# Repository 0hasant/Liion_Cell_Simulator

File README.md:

# Cell Test Bench

Single-cell characterization bench for 18650 and 21700 Li-ion cells (DMEGC INR45E, generic 3.5 Ah 18650). The goal is a fitted **2RC equivalent-circuit model** (OCV, R0, R1/C1, R2/C2 versus SOC and temperature). Part of the Solaris final-year project.

- 0–10 A linear electronic load (constant current), down to 2.0 V
- Charging up to 5 A from a 30 V bench PSU through an XL4016 module, with voltage **and** current limit set by the MCU
- Bidirectional current on one 10 mΩ shunt with Kelvin taps; Kelvin cell voltage on a 16-bit ADS1115
- Cell held at about 10–45 °C in an insulated pocket, cooled or heated by two TEC1-12706 Peltiers
- STM32F103 Blue Pill, USB CDC to a Python UI
- Hardware protection (OV, UV, OC, OT) that latches and cuts relay and Peltier power without the firmware

## Status (v0.4, 2026-11-11)

| Item | State |
|---|---|
| Schematic | v0.4, 8 sheets, generated by `hardware/tools/design.py`. Netlist checked against KiCad's export (0 problems). All review items closed: `docs/CHANGES_v0.4.md` |
| Parts | Every part has a Turkish source with price and stock on 2026-11-10: `hardware/bom.csv` (board) and `hardware/bom_offboard.csv` (modules, mechanics). Total about 5,500 TL |
| PCB | 180 × 130 mm, **single-sided** for in-house CNC milling, through-hole parts plus two SMD parts on the copper side, wire jumpers where one layer is not enough |
| CNC files | `hardware/fab/`: Gerber + Excellon, mirrored SVGs for Luban, 1:1 print, jumper list, DRC report. How to mill: `docs/CNC_MILLING.md` |
| 3D | Electronics box and thermal unit in `mechanical/` (STL, STEP, renders). All printed parts fit a 220 × 220 mm bed, collision check clean |
| Built / tested | **No.** Bring-up plan: `docs/BRINGUP.md` |
| Firmware, UI | Not started |

## Repository layout

| Path | Contents |
|---|---|
| `hardware/kicad/` | KiCad project: open `cell_test_bench.kicad_pro` (KiCad 7 format, opens in KiCad 10) |
| `hardware/kicad/lib/` | Project footprint library and 3D models |
| `hardware/fab/` | Milling and drilling files |
| `hardware/bom.csv`, `bom_offboard.csv` | Priced BOM with Turkish shops and links |
| `hardware/tools/` | Scripts that generate the schematic, placement, routing, BOM and fab files |
| `mechanical/` | CadQuery enclosure: `enclosure.py`, `check.py`, STL, STEP, renders |
| `docs/` | Schematic guide, v0.4 changes, bring-up, milling, layout review, project sync |
| `firmware/`, `ui/` | Not started |

## Board overview

- **Left edge:** PSU input (J101), 12 V buck module (J102), charger module (J401), FB tap (J402).
- **Top edge:** thermostat (J104), fans (J704–J706), Peltier output (J702), Blue Pill with USB at the edge.
- **Right edge:** four NTC terminals (J501–J504).
- **Bottom edge:** cell power (J205), 0.1 Ω load resistor (J301), IRFP260N (Q301, tab facing out onto the load cooler), Kelvin sense (J206).
- `PGND` (power return) and `GND` (signal) are separate nets, joined at one wire link (JP201) next to the shunt.

## Blue Pill pin map

| Pin | Signal | Function |
|---|---|---|
| PA0 / PA1 | I_MON / V_FAST | ADC: fast current (1.71 V + 0.12 V/A), fast cell voltage ÷ 2 |
| PA2–PA5 | NTC_CELL, NTC_AIR, NTC_HS, NTC_TEC | ADC: temperatures |
| PA6 / PA7 / PB0 | PWM_L / PWM_C / PWM_I | TIM3: load setpoint, charger voltage, charger current limit |
| PA8 | FAN_PWM | TIM1_CH1: both cooler fans |
| PA9 / PA10 | DBG_TX / DBG_RX | Debug UART (J803) |
| PB6 / PB7 | SCL / SDA | I2C1: ADS1115 at 0x48 |
| PB8 / PB9 | TEC_PWM / TEC_DIR | Peltier power (TIM4) and heat/cool relay |
| PB10 | ARM | High-Z normally; high pulse = re-arm protection, low = force trip |
| PB12 / PB13 | K1_EN / K2_EN | Charger relay / load relay |
| PB14 | LOAD_OFF | Open drain; low = load enabled |
| PB15 | FAULT_N | Low = protection tripped |

## Key design numbers

- Load: `I ≈ (PWM × 0.119 V − 5 mV) / 10 mΩ`, full scale about 11.3 A; firmware closes the loop on the ADS1115.
- Charger: CV trimmer set to **4.25 V** (hardware ceiling); hardware current limit 0–5.6 A.
- Trips: OV > 4.33 V, UV < 1.96 V, discharge > 11.6 A, charge > 6.2 A, heatsink or cell > about 61 °C. Latched; power-up state is tripped.

## Regenerating

```
cd hardware/tools
python3 design.py ../kicad                         # schematic (overwrites the KiCad sheets)
python3 makelib.py ../kicad                        # project footprint library + 3D models
kicad-cli sch export netlist --format kicadsexpr -o /tmp/net.net ../kicad/cell_test_bench.kicad_sch
python3 verify.py /tmp/net.net                     # netlist vs design
python3 pcbgen.py /tmp/net.net ../kicad 1          # outline + placement (overwrites the PCB)
python3 route2.py ../kicad/cell_test_bench.kicad_pcb /tmp/routed.kicad_pcb 32   # single-sided router, ~30 min
python3 cleanup.py /tmp/routed.kicad_pcb ../kicad/cell_test_bench.kicad_pcb
python3 fab.py ../kicad/cell_test_bench.kicad_pcb ../fab
python3 bom.py ../bom.csv ../bom_offboard.csv
```

Once you edit the board or schematic in KiCad by hand, those files are the source of truth: don't re-run the generators after that.

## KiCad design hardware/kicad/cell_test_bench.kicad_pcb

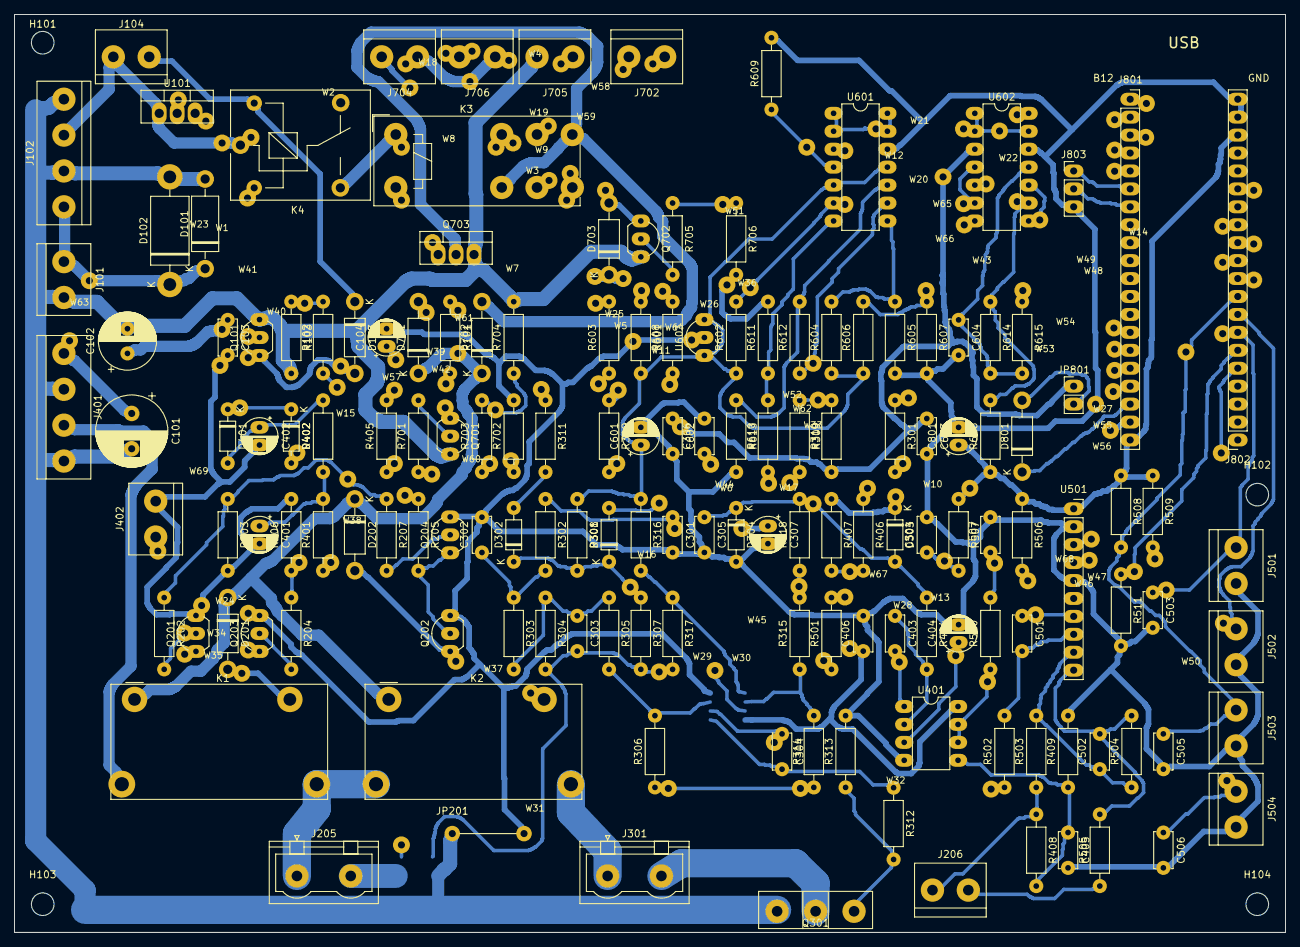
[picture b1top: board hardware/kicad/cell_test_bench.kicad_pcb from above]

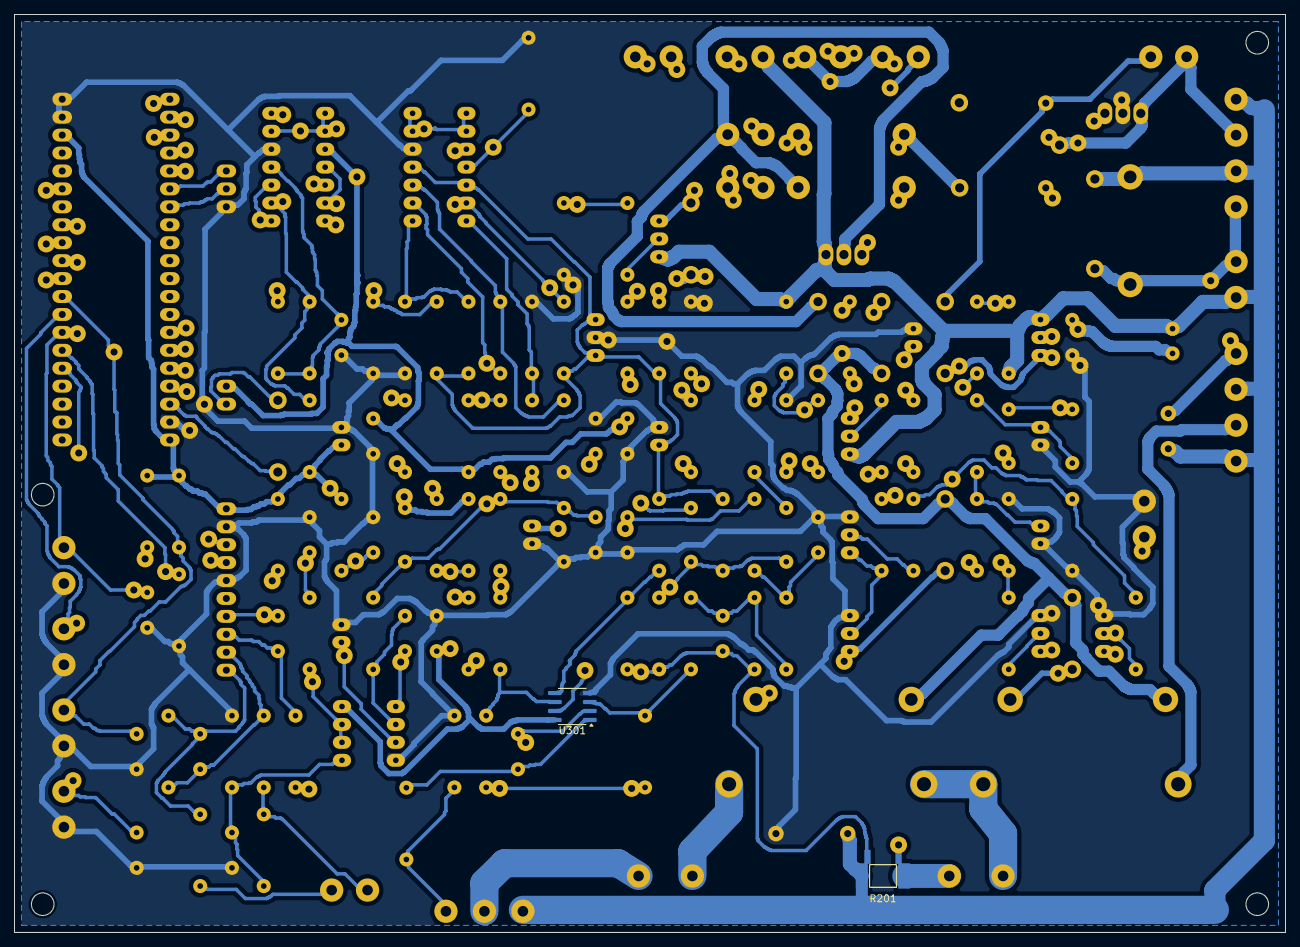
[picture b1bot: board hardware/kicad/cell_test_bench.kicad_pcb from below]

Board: 2 copper layers, 180.0 x 130.0 mm, 228 parts (2 on the bottom side), 91 nets.

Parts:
C101: 100uF 50V; CP_Radial_D10.0mm_P5.00mm
C102: 220uF 25V; CP_Radial_D8.0mm_P3.50mm
C103, C303, C306, C403, C406, C501, C502, C503, C504, C505, C506, C602, C603: 100nF; C_Disc_D5.0mm_W2.5mm_P5.00mm
C104, C307, C401, C402, C404, C601, C801: 10uF 25V; CP_Radial_D5.0mm_P2.50mm
C301, C302: 1uF; C_Disc_D5.0mm_W2.5mm_P5.00mm
C304: 1nF; C_Disc_D5.0mm_W2.5mm_P5.00mm
C305, C405, C507, C604: 10nF; C_Disc_D5.0mm_W2.5mm_P5.00mm
D101: P6KE39CA (TVS); D_DO-15_P12.70mm_Horizontal
D102: 1N5408; D_DO-201AD_P15.24mm_Horizontal
D103, D201, D202, D701, D702, D703, D801: 1N5819; D_DO-41_SOD81_P10.16mm_Horizontal
D301, D302: 1N4148; D_DO-35_SOD27_P7.62mm_Horizontal
D303, D304, D401, D402: BAT85; D_DO-35_SOD27_P7.62mm_Horizontal
H101, H102, H103, H104: M3 mounting hole; MountingHole_3.2mm_M3
J101: PSU in 30V (+, -) via inline 5A fuse; TerminalBlock_bornier-2_P5.08mm
J102: 12V buck XL4016: IN+ IN- OUT+ OUT-; TerminalBlock_bornier-4_P5.08mm
J104: Thermostat 60C NC (on load heatsink); TerminalBlock_bornier-2_P5.08mm
J205: Cell power to pocket (+, -) via inline 15A fuse; PhoenixContact_GMSTBVA_2,5_2-G-7,62_1x02_P7.62mm_Vertical
J206: Cell Kelvin sense (+, -); TerminalBlock_bornier-2_P5.08mm
J301: Series R 0.1R 50W alu (off-board); PhoenixContact_GMSTBVA_2,5_2-G-7,62_1x02_P7.62mm_Vertical
J401: XL4016 CC/CV module: IN+ IN- OUT+ OUT-; TerminalBlock_bornier-4_P5.08mm
J402: XL4016 FB tap (pin 1 to the FB pin; pin 2 spare G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; TerminalBlock_bornier-2_P5.08mm
J501: NTC 10k cell; TerminalBlock_bornier-2_P5.08mm
J502: NTC 10k air; TerminalBlock_bornier-2_P5.08mm
J503: NTC 10k hs; TerminalBlock_bornier-2_P5.08mm
J504: NTC 10k tec; TerminalBlock_bornier-2_P5.08mm
J702: Peltier 2x TEC1-12706 in series (A, B); TerminalBlock_bornier-2_P5.08mm
J704: Fan 12V load heatsink (+,-); TerminalBlock_bornier-2_P5.08mm
J705: Pocket mixing fan 12V (+,-); TerminalBlock_bornier-2_P5.08mm
J706: Fan 12V Peltier hot side (+,-); TerminalBlock_bornier-2_P5.08mm
J801: Blue Pill header A: B12 B13 B14 B15 A8 A9 A10 A11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; PinSocket_1x20_P2.54mm_Vertical
J802: Blue Pill header B: VB C13 C14 C15 A0 A1 A2 A3 A4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; PinSocket_1x20_P2.54mm_Vertical
J803: Debug UART: TX RX GND; PinHeader_1x03_P2.54mm_Vertical
JP201: GND-PGND link (wire); WireLink_P10.16mm
JP801: Board 5V to Blue Pill (normally open); PinHeader_1x02_P2.54mm_Vertical
K1: ALFG2PF121 (charge); Relay_SPST_Panasonic_ALFG_FormA_CircularHoles
K2: ALFG2PF121 (load); Relay_SPST_Panasonic_ALFG_FormA_CircularHoles
K3: HK14FD-DC12V-SHG (DPDT, polarity); Relay_DPDT_Finder_40.52
K4: SRD-12VDC-SL-C (safety); Relay_SPDT_SANYOU_SRD_Series_Form_C
Q101, Q201, Q202, Q701, Q702: BC337; TO-92_Inline_Wide
Q203, Q204: BC547; TO-92_Inline_Wide
Q301: IRFP260N; TO-247-3_Vertical
Q703: IRLZ44N; TO-220-3_Vertical
R101, R102: 2.2k; R_Axial_DIN0207_L6.3mm_D2.5mm_P10.16mm_Horizontal
R103: 4.7k; R_Axial_DIN0207_L6.3mm_D2.5mm_P10.16mm_Horizontal
R201: 10mR 1% 2.5W 2512; R_Shunt_2512_Kelvin
R202, R205, R304, R314, R317, R318, R601, R701: 1k; R_Axial_DIN0207_L6.3mm_D2.5mm_P10.16mm_Horizontal
R203, R204, R206, R207, R301, R302, R305, R306, R307, R310, R313, R406, R408, R503, R504, R506, R507, R508, R509, R510, R511, R602, R603, R605, R615, R616, R702, R704, R706: 10k; R_Axial_DIN0207_L6.3mm_D2.5mm_P10.16mm_Horizontal
R303: 6.8k; R_Axial_DIN0207_L6.3mm_D2.5mm_P10.16mm_Horizontal
R308: 10M; R_Axial_DIN0207_L6.3mm_D2.5mm_P10.16mm_Horizontal
R309, R613, R614: 100k; R_Axial_DIN0207_L6.3mm_D2.5mm_P10.16mm_Horizontal
R311: 150k; R_Axial_DIN0207_L6.3mm_D2.5mm_P10.16mm_Horizontal
R312, R319, R501, R502, R505, R703: 100R; R_Axial_DIN0207_L6.3mm_D2.5mm_P10.16mm_Horizontal
R315: 12k; R_Axial_DIN0207_L6.3mm_D2.5mm_P10.16mm_Horizontal
R316: 18k; R_Axial_DIN0207_L6.3mm_D2.5mm_P10.16mm_Horizontal
R401, R402: 560R; R_Axial_DIN0207_L6.3mm_D2.5mm_P10.16mm_Horizontal
R404, R609: 15k; R_Axial_DIN0207_L6.3mm_D2.5mm_P10.16mm_Horizontal
R405: 3.3k; R_Axial_DIN0207_L6.3mm_D2.5mm_P10.16mm_Horizontal
R407: 22k; R_Axial_DIN0207_L6.3mm_D2.5mm_P10.16mm_Horizontal
R409: 1M; R_Axial_DIN0207_L6.3mm_D2.5mm_P10.16mm_Horizontal
R604, R611: 16k; R_Axial_DIN0207_L6.3mm_D2.5mm_P10.16mm_Horizontal
R606: 27k; R_Axial_DIN0207_L6.3mm_D2.5mm_P10.16mm_Horizontal
R607, R610: 9.1k; R_Axial_DIN0207_L6.3mm_D2.5mm_P10.16mm_Horizontal
R608: 11k; R_Axial_DIN0207_L6.3mm_D2.5mm_P10.16mm_Horizontal
R612: 24k; R_Axial_DIN0207_L6.3mm_D2.5mm_P10.16mm_Horizontal
R705: 470R; R_Axial_DIN0207_L6.3mm_D2.5mm_P10.16mm_Horizontal
U101: L7805CV; TO-220-3_Vertical
U301: OPA2171AIDR; SOIC-8_3.9x4.9mm_P1.27mm
U401: LM358P; DIP-8_W7.62mm
U501: ADS1115 module (ADDR=GND): VDD GND SCL SDA ADDR A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; PinSocket_1x10_P2.54mm_Vertical
U601, U602: LM339N; DIP-14_W7.62mm
U603: TL431 (TO-92); TO-92_Inline_Wide
W1, W2, W3, W4, W5: wire +12V; WireJumper
W6: wire +12VA; WireJumper
W7, W8, W9: wire +12V_SW; WireJumper
W10: wire +3V3; WireJumper
W11, W12: wire +5V; WireJumper
W13: wire ADC_IG; WireJumper
W14: wire ARM; WireJumper
W15: wire CC_INJ; WireJumper
W16: wire CC_OUT; WireJumper
W17: wire DL1; WireJumper
W18, W19: wire FAN_N; WireJumper
W20: wire FAN_PWM; WireJumper
W21, W22: wire FAULT_N; WireJumper
W23, W24, W25, W26, W27: wire GND; WireJumper
W28: wire ILIM; WireJumper
W29: wire INN; WireJumper
W30: wire ISNS_G; WireJumper
W31, W32: wire ISNS_N; WireJumper
W33: wire I_MON; WireJumper
W34: wire K1_B; WireJumper
W35: wire K1_COIL; WireJumper
W36: wire K1_EN; WireJumper
W37: wire K2_COIL; WireJumper
W38: wire K2_EN; WireJumper
W39: wire K3_COIL; WireJumper
W40: wire K4_B; WireJumper
W41, W42: wire K4_COIL; WireJumper
W43: wire LOAD_OFF; WireJumper
W44: wire LOFF_K; WireJumper
W45: wire MON_RAW; WireJumper
W46: wire NTC_AIR; WireJumper
W47, W48: wire NTC_CELL; WireJumper
W49: wire NTC_HS; WireJumper
W50: wire NTC_TEC; WireJumper
W51: wire OV_DIV; WireJumper
W52: wire PWM_C; WireJumper
W53: wire PWM_I; WireJumper
W54: wire PWM_L; WireJumper
W55: wire SCL; WireJumper
W56: wire SDA; WireJumper
W57: wire SW_B; WireJumper
W58: wire TEC_A; WireJumper
W59: wire TEC_B; WireJumper
W60: wire TEC_DIR; WireJumper
W61: wire TEC_G; WireJumper
W62: wire TEC_PWM; WireJumper
W63: wire VIN; WireJumper
W64, W65: wire VREF_H; WireJumper
W66: wire VREF_T; WireJumper
W67: wire V_CELL; WireJumper
W68: wire V_FAST; WireJumper
W69: wire XL_FB; WireJumper

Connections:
+3V3: C801.1, D303.1, J801.20, J802.18, R407.1, R506.1, R507.1, R508.1, R509.1, R616.1, U501.1, W10.1, W10.2
+5V: C104.1, C602.1, C603.1, JP801.1, R101.1, R310.1, R601.1, U101.3, U601.3, U602.3, W11.1, W11.2, W11.3, W11.4, W11.5, W12.1, W12.2
+12V: C102.1, C103.1, D703.1, J102.3, J104.1, J704.1, J705.1, J706.1, K4.1, R319.1, U101.1, W1.1, W1.2, W2.1, W2.2, W3.1, W3.2, W4.1, W4.2, W5.1, W5.2
+12VA: C306.1, C307.1, C406.1, R319.2, U301.8, U401.8, W6.1, W6.2, W6.3, W6.4
+12V_SW: D201.1, D202.1, D701.1, D702.1, K1.A1, K2.A1, K3.12, K3.24, K3.A1, K4.3, W7.1, W7.2, W8.1, W8.2, W9.1, W9.2
/Cell_Relays/CELL_N: J205.2, R201.1
/Cell_Relays/CELL_P: J205.1, K1.14, K2.11
/Cell_Relays/K1_B: Q201.2, Q203.1, R202.2, W34.1, W34.2
/Cell_Relays/K1_COIL: D201.2, K1.A2, Q201.1, W35.1, W35.2
/Cell_Relays/K1_IB: Q203.2, R204.2
/Cell_Relays/K2_B: Q202.2, Q204.1, R205.2
/Cell_Relays/K2_COIL: D202.2, K2.A2, Q202.1, W37.1, W37.2
/Cell_Relays/K2_IB: Q204.2, R207.2
/Charger/CCN: C403.1, R404.2, U401.2
/Charger/CC_INJ: D402.2, R405.2, W15.1, W15.2
/Charger/CC_OUT: C403.2, R405.1, U401.1, W16.1, W16.2
/Charger/DAC_C: C402.1, D401.2, R402.2
/Charger/DC1: C401.1, R401.2, R402.1
/Charger/ILIM: C404.1, R406.2, R407.2, U401.3, W28.1, W28.2
/Charger/SBUF: C405.1, R408.2, R409.1, U401.5
/Charger/XL_FB: D401.1, D402.1, J402.1, W69.1, W69.2
/Electronic_Load/DAC_L: C302.1, R302.2, R303.1
/Electronic_Load/DL1: C301.1, R301.2, R302.1, W17.1, W17.2
/Electronic_Load/FLT_K: D302.2, R311.2
/Electronic_Load/GATE: Q301.1, R312.2, R313.1
/Electronic_Load/INN: C304.1, D301.1, D302.1, R307.1, R308.2, U301.2, W29.1, W29.2
/Electronic_Load/INP: R305.2, R306.2, U301.3
/Electronic_Load/LOAD_D: J301.2, Q301.2
/Electronic_Load/LOFF_K: D301.2, R309.2, W44.1, W44.2
/Electronic_Load/MB: R316.2, R317.1, U301.5
/Electronic_Load/MN: R314.2, R315.1, U301.6
/Electronic_Load/MON_RAW: R315.2, R318.1, U301.7, W45.1, W45.2
/Electronic_Load/OA_OUT: C304.2, R312.1, U301.1
/Electronic_Load/SETP: C303.1, R303.2, R304.1, R305.1
/MCU/BP_5V: D801.1, J801.18
/MCU/BP_J: D801.2, JP801.2
/MCU/DBG_RX: J801.7, J803.2
/MCU/DBG_TX: J801.6, J803.1
/Measurement/ADC_IG: C501.1, R501.2, U501.7, W13.1, W13.2
/Measurement/ADC_IN: C501.2, R502.2, U501.8
/Measurement/ADC_VN: C502.2, R504.2, R505.2, U501.10
/Measurement/ADC_VP: C502.1, R503.2, R504.1, U501.9
/Power/K4_B: Q101.2, R102.2, R103.1, W40.1, W40.2
/Power/TSTAT: D103.1, J104.2, K4.5
/Protection/ID_DIV: R612.2, R613.1, U601.10
/Protection/LATCH_IN: C604.1, R614.2, R615.2, U602.11
/Protection/OV_DIV: R608.2, R609.1, U601.4, W51.1, W51.2
/Protection/UV_DIV: R610.2, R611.1, U601.7
/Protection/VREF_C: R604.2, R605.1, U601.8
/Protection/VREF_H: R602.2, R603.1, U601.6, U602.8, U602.10, W64.1, W64.2, W65.1, W65.2
/Protection/VREF_T: R606.2, R607.1, U602.4, U602.6, W66.1, W66.2
/Thermal/FAN_B: Q702.2, R705.2
/Thermal/FAN_N: D703.2, J704.2, J706.2, Q702.1, W18.1, W18.2, W19.1, W19.2
/Thermal/K3_B: Q701.2, R701.2
/Thermal/K3_COIL: D701.2, K3.A2, Q701.1, W39.1, W39.2, W39.3
/Thermal/TEC_A: J702.1, K3.11, W58.1, W58.2
/Thermal/TEC_B: J702.2, K3.21, W59.1, W59.2
/Thermal/TEC_G: Q703.1, R703.2, R704.1, W61.1, W61.2
/Thermal/TEC_SW: D702.2, K3.14, K3.22, Q703.2
ARM: J802.15, R615.1, W14.1, W14.2
CHG_OUT: J401.3, K1.11
FAN_PWM: J801.5, R705.1, R706.1, W20.1, W20.2
FAULT_N: J801.4, R614.1, R616.2, U601.1, U601.2, U601.13, U601.14, U602.1, U602.2, U602.9, U602.13, W21.1, W21.2, W22.1, W22.2, W22.3
GND: C103.2, C104.2, C301.2, C302.2, C305.2, C306.2, C307.2, C401.2, C402.2, C404.2, C405.2, C406.2, C503.2, C504.2, C505.2, C506.2, C507.2, C601.2, C602.2, C603.2, C604.2, C801.2, D304.2, J402.2, J501.2, J502.2, J503.2, J504.2, J801.19, J802.19, J802.20, J803.3, JP201.2, Q201.3, Q202.3, Q203.3, Q204.3, R203.2, R206.2, R313.2, R409.2, R511.2, R603.2, R605.2, R607.2, R609.2, R611.2, R613.2, R702.2, R706.2, U101.2, U301.4, U401.4, U501.2, U501.5, U601.12, U602.12, U603.2, W23.1, W23.2, W24.1, W24.2, W25.1, W25.2, W26.1, W26.2, W27.1, W27.2
ISNS_G: C303.2, R201.3, R304.2, R307.2, R317.2, R501.1, W30.1, W30.2
ISNS_N: R201.2, R306.1, R314.1, R502.1, W31.1, W31.2, W32.1, W32.2
I_MON: C305.1, D303.2, D304.1, J802.5, R318.2, R404.1, R612.1, U601.9, W33.1, W33.2, W33.3
K1_EN: J801.1, R202.1, R203.1, R207.1, W36.1, W36.2
K2_EN: J801.2, R204.1, R205.1, R206.1, W38.1, W38.2, W38.3
K4_COIL: D103.2, K4.2, Q101.1, R311.1, W41.1, W41.2, W42.1, W42.2
LOAD_OFF: J801.3, R309.1, R310.2, W43.1, W43.2
LOAD_P: J301.1, K2.14
NTC_AIR: C504.1, J502.1, J802.8, R507.2, W46.1, W46.2
NTC_CELL: C503.1, J501.1, J802.7, R506.2, U602.7, W47.1, W47.2, W48.1, W48.2
NTC_HS: C505.1, J503.1, J802.9, R508.2, U602.5, W49.1, W49.2
NTC_TEC: C506.1, J504.1, J802.10, R509.2, W50.1, W50.2, W50.3
PGND: C101.2, C102.2, D101.2, D102.2, J101.2, J102.2, J102.4, J401.2, J401.4, J705.2, JP201.1, Q101.3, Q301.3, Q701.3, Q702.3, Q703.3, R103.2, R201.4, R704.2
PWM_C: J802.12, R401.1, W52.1, W52.2
PWM_I: J802.13, R406.1, W53.1, W53.2
PWM_L: J802.11, R301.1, W54.1, W54.2
SCL: J801.14, U501.3, W55.1, W55.2
SDA: J801.15, U501.4, W56.1, W56.2
SENSE_N: J206.2, R505.1
SENSE_P: J206.1, R408.1, R503.1
SW_B: R101.2, R102.1, U602.14, W57.1, W57.2, W57.3
TEC_DIR: J801.17, R701.1, R702.1, W60.1, W60.2, W60.3
TEC_PWM: J801.16, R703.1, W62.1, W62.2
VIN: C101.1, D101.1, D102.1, J101.1, J102.1, J401.1, W63.1, W63.2
VREF: C601.1, R308.1, R316.1, R601.2, R602.1, R604.1, R606.1, U601.5, U601.11, U603.1, U603.3
V_CELL: R510.1, R608.1, R610.1, U401.6, U401.7, W67.1, W67.2, W67.3
V_FAST: C507.1, J802.6, R510.2, R511.1, W68.1, W68.2

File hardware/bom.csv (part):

Qty,References,Value,Footprint,Buy,Shop,Unit TL (VAT incl.),Line TL,Stock 2026-11-10,Link,Note
1,C101,100uF 50V,CP_Radial_D10.0mm_P5.00mm,"electrolytic 100 uF 50 V, D10 P5",Direnc.net,4.00,4.00,"generic, price estimated",,
1,C102,220uF 25V,CP_Radial_D8.0mm_P3.50mm,"electrolytic 220 uF 25 V, D8 P3.5",Direnc.net,3.00,3.00,"generic, price estimated",,
13,C103 C303 C306 C403 C406 C501 C502 C503 C504 C505 C506 C602 C603,100nF,C_Disc_D5.0mm_W2.5mm_P5.00mm,"ceramic capacitor, radial, 5 mm pitch, 50 V",Direnc.net,0.98,12.74,in stock (100 nF checked),https://www.direnc.net/100nf-63v-seramik,"1 nF / 10 nF / 1 uF: same series, price similar"
7,C104 C307 C401 C402 C404 C601 C801,10uF 25V,CP_Radial_D5.0mm_P2.50mm,"electrolytic 10 uF 25 V (or 50 V), D5 P2.5",Direnc.net,1.50,10.50,"generic, price estimated",,
2,C301 C302,1uF,C_Disc_D5.0mm_W2.5mm_P5.00mm,"ceramic capacitor, radial, 5 mm pitch, 50 V",Direnc.net,0.98,1.96,in stock (100 nF checked),https://www.direnc.net/100nf-63v-seramik,"1 nF / 10 nF / 1 uF: same series, price similar"
1,C304,1nF,C_Disc_D5.0mm_W2.5mm_P5.00mm,"ceramic capacitor, radial, 5 mm pitch, 50 V",Direnc.net,0.98,0.98,in stock (100 nF checked),https://www.direnc.net/100nf-63v-seramik,"1 nF / 10 nF / 1 uF: same series, price similar"
4,C305 C405 C507 C604,10nF,C_Disc_D5.0mm_W2.5mm_P5.00mm,"ceramic capacitor, radial, 5 mm pitch, 50 V",Direnc.net,0.98,3.92,in stock (100 nF checked),https://www.direnc.net/100nf-63v-seramik,"1 nF / 10 nF / 1 uF: same series, price similar"
1,D101,P6KE39CA (TVS),D_DO-15_P12.70mm_Horizontal,P6KE39CA TVS 600 W DO-15,Direnc.net,12.79,12.79,in stock,https://www.direnc.net/p6ke39ca-do-15-371v-600w-tvs-diyot,
1,D102,1N5408,D_DO-201AD_P15.24mm_Horizontal,1N5408 3 A DO-201,Direnc.net,2.72,2.72,in stock,https://www.direnc.net/1n5408-rectifiers-1000v-3a--mic,
7,D103 D201 D202 D701 D702 D703 D801,1N5819,D_DO-41_SOD81_P10.16mm_Horizontal,1N5819 Schottky 1 A 40 V DO-41,Direnc.net,1.57,10.99,in stock,https://www.direnc.net/1n5819-1a-40v-schottky-rectifier-mic,"1N4007 was sold out, 1N5819 does the same job here"
2,D301 D302,1N4148,D_DO-35_SOD27_P7.62mm_Horizontal,1N4148 DO-35,Robotistan,0.79,1.58,in stock,https://www.robotistan.com/1n4148-100v-450ma-aksiyel-tipli-h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,sold out at Direnc
4,D303 D304 D401 D402,BAT85,D_DO-35_SOD27_P7.62mm_Horizontal,BAT85 Schottky DO-35,Direnc.net,2.03,8.12,in stock,https://www.direnc.net/bat85-schottky-diodes-rectifiers-scho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,
2,J101 J702,"PSU in 30V (+, -) via inline 5A fuse",TerminalBlock_bornier-2_P5.08mm,"2-pin 5.08 mm screw terminal (""1 No"")",Direnc.net,4.84,9.68,in stock,https://www.direnc.net/1-numara-2li-klemens,
2,J102 J401,12V buck XL4016: IN+ IN- OUT+ OUT-,TerminalBlock_bornier-4_P5.08mm,4-pin 5.08 mm screw terminal (two 2-pin blocks slid together),Direnc.net,9.68,19.36,in stock,https://www.direnc.net/1-numara-2li-klemens,
10,J104 J206 J402 J501 J502 J503 J504 J704 J706 J705,Thermostat 60C NC (on load heatsink),TerminalBlock_bornier-2_P5.08mm,"2-pin 5.08 mm screw terminal (""0 No"")",Direnc.net,3.45,34.50,in stock,https://www.direnc.net/0-numara-2li-klemens-1,"sensor, fan, thermostat and FB wires"
2,J205 J301,"Cell power to pocket (+, -) via inline 15A fuse","PhoenixContact_GMSTBVA_2,5_2-G-7,62_1x02_P7.62mm_Vertical","2-pin 7.62 mm pluggable terminal, header 180 deg + plug",Direnc.net,13.21,26.42,in stock,https://www.direnc.net/2-pin-762mm-90-gecmeli-takim-klemens-12424,plug: https://www.direnc.net/2-pin-762mm-90-gecmeli-takim-klemens
2,J801 J802,Blue Pill header A: B12 B13 B14 B15 A8 A9 A10 A11 A12 A15 B3 B4 B5 B6 B7 B8 B9 5V GND 3V3,PinSocket_1x20_P2.54mm_Vertical,"1x40 precision (machined) female header 2.54 mm, cut to 1x20",Direnc.net,21.17,42.34,in stock,https://www.direnc.net/1x40-precision-disi-header,the plain 1x40 female header (6.05 TL) was sold out; cutting a machined strip costs one pin
1,J803,Debug UART: TX RX GND,PinHeader_1x03_P2.54mm_Vertical,1x40 male pin header 2.54 mm (cut),Direnc.net,5.00,5.00,"generic, price estimated",,
1,JP201,GND-PGND link (wire),WireLink_P10.16mm,wire link (resistor leg or 0.8 mm copper wire),-,0.00,0.00,-,,
1,JP801,Board 5V to Blue Pill (normally open),PinHeader_1x02_P2.54mm_Vertical,1x40 male pin header 2.54 mm (cut),Direnc.net,5.00,5.00,"generic, price estimated",,
2,K1 K2,ALFG2PF121 (charge),Relay_SPST_Panasonic_ALFG_FormA_CircularHoles,"Panasonic ALFG2PF121, 12 V, 33 A",Ozdisan,148.90,297.80,28609 in stock,https://ozdisan.com/elektromekanik-komponentler/roleler-ve-r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,USD 2.64 + VAT
1,K3,"HK14FD-DC12V-SHG (DPDT, polarity)",Relay_DPDT_Finder_40.52,"Huike HK14FD-DC12V-SHG, DPDT 5 A, 12 V (""4052"" type)",Direnc.net,72.59,72.59,in stock,https://www.direnc.net/12v-cift-kontak-huike-4052-12v-10a,alternative: Tianbo TRA3-L-12VDC-S-2Z (116 TL)
1,K4,SRD-12VDC-SL-C (safety),Relay_SPDT_SANYOU_SRD_Series_Form_C,"Songle SRD-12VDC-SL-C, 10 A",Robotistan,20.68,20.68,in stock,https://www.robotistan.com/12v-10a-tek-kontak-role-srd12vdcslc,
5,Q101 Q201 Q202 Q701 Q702,BC337,TO-92_Inline_Wide,BC337 NPN TO-92,Direnc.net,1.21,6.05,in stock,https://www.direnc.net/bc337-transistor-bjt-npn-to-92,
2,Q203 Q204,BC547,TO-92_Inline_Wide,BC547 NPN TO-92,Direnc.net,1.28,2.56,in stock,https://www.direnc.net/bc547-transistor-bjt-npn-to-92,
1,Q301,IRFP260N,TO-247-3_Vertical,IRFP260NPBF TO-247,Ozdisan,43.43,43.43,4451 in stock,https://www.ozdisan.com/en/p/discrete-mosfets-435/infineon-i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,USD 0.77 + VAT; Direnc lists IRFP260M at 69.87 TL (sold out on the check date)
1,Q703,IRLZ44N,TO-220-3_Vertical,IRLZ44NPBF TO-220 (VBsemi),Robotistan,24.46,24.46,in stock,https://www.robotistan.com/vbsemi-elec-irlz44npbf-vb,TO-220 was sold out at Direnc
2,R101 R102,2.2k,R_Axial_DIN0207_L6.3mm_D2.5mm_P10.16mm_Horizontal,1/4 W 1 % metal film resistor (E24 value),Direnc.net,0.67,1.34,in stock (series),https://www.direnc.net/14w-metal-film-direnc,check each value in the cart; all values used are E24
1,R103,4.7k,R_Axial_DIN0207_L6.3mm_D2.5mm_P10.16mm_Horizontal,1/4 W 1 % metal film resistor (E24 value),Direnc.net,0.67,0.67,in stock (series),https://www.direnc.net/14w-metal-film-direnc,check each value in the cart; all values used are E24
1,R201,10mR 1% 2.5W 2512,R_Shunt_2512_Kelvin,"Isabellenhuette CMS 10 mOhm 1 % 2.5 W, 2512",Direnc.net,39.63,39.63,in stock,https://www.direnc.net/10mr-2515-sont-direnc,"listed as ""10mR 2515""; datasheet says size 2512"
8,R202 R205 R304 R314 R317 R318 R601 R701,1k,R_Axial_DIN0207_L6.3mm_D2.5mm_P10.16mm_Horizontal,1/4 W 1 % metal film resistor (E24 value),Direnc.net,0.67,5.36,in stock (series),https://www.direnc.net/14w-metal-film-direnc,check each value in the cart; all values used are E24
29,R203 R204 R206 R207 R301 R302 R305 R306 R307 R310 R313 R406 R408 R503 R504 R506 R507 R508 R509 R510 R511 R602 R603 R605 R615 R616 R702 R704 R706,10k,R_Axial_DIN0207_L6.3mm_D2.5mm_P10.16mm_Horizontal,1/4 W 1 % metal film resistor (E24 value),Direnc.net,0.67,19.43,in stock (series),https://www.direnc.net/14w-metal-film-direnc,check each value in the cart; all values used are E24
1,R303,6.8k,R_Axial_DIN0207_L6.3mm_D2.5mm_P10.16mm_Horizontal,1/4 W 1 % metal film resistor (E24 value),Direnc.net,0.67,0.67,in stock (series),https://www.direnc.net/14w-metal-film-direnc,check each value in the cart; all values used are E24
1,R308,10M,R_Axial_DIN0207_L6.3mm_D2.5mm_P10.16mm_Horizontal,1/4 W 1 % metal film resistor (E24 value),Direnc.net,0.67,0.67,in stock (series),https://www.direnc.net/14w-metal-film-direnc,check each value in the cart; all values used are E24
3,R309 R613 R614,100k,R_Axial_DIN0207_L6.3mm_D2.5mm_P10.16mm_Horizontal,1/4 W 1 % metal film resistor (E24 value),Direnc.net,0.67,2.01,in stock (series),https://www.direnc.net/14w-metal-film-direnc,check each value in the cart; all values used are E24
1,R311,150k,R_Axial_DIN0207_L6.3mm_D2.5mm_P10.16mm_Horizontal,1/4 W 1 % metal film resistor (E24 value),Direnc.net,0.67,0.67,in stock (series),https://www.direnc.net/14w-metal-film-direnc,check each value in the cart; all values used are E24
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
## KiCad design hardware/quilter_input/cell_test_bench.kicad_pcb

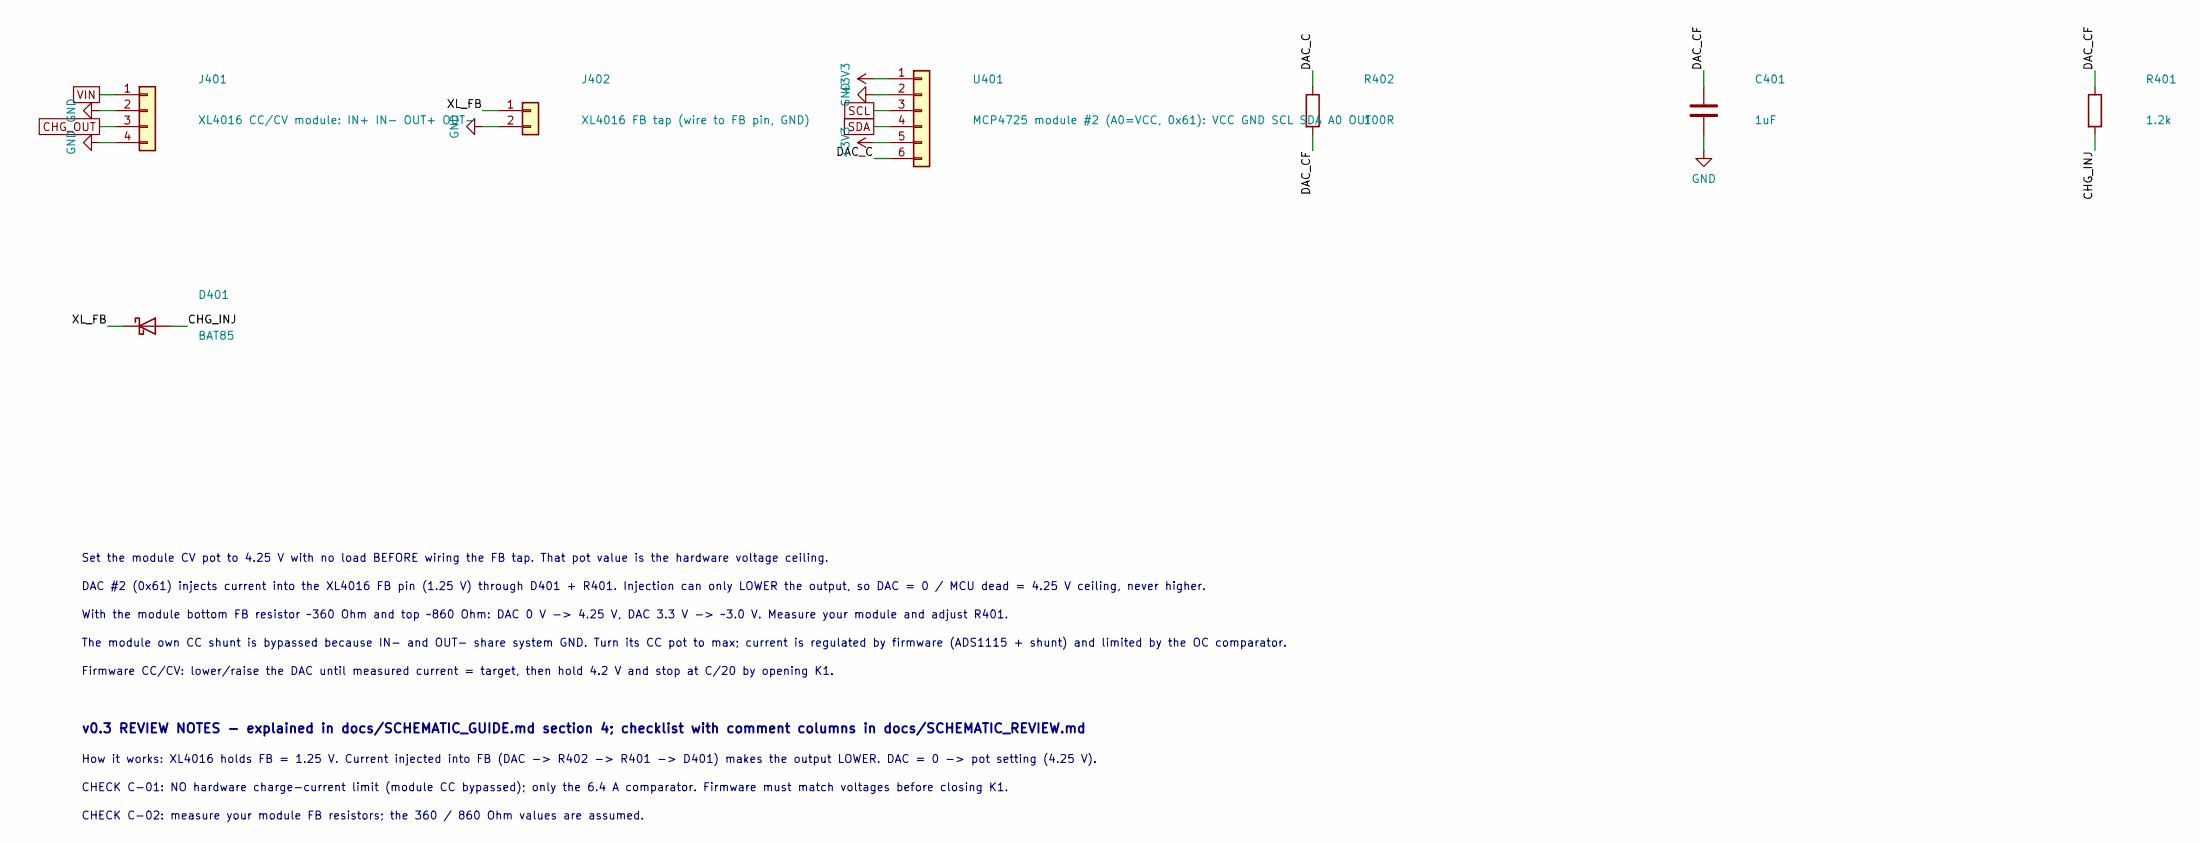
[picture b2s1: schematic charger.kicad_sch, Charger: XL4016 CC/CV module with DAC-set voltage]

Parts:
C401: 1uF; C_1206_3216Metric
D401: BAT85; D_DO-35_SOD27_P7.62mm_Horizontal; MPN BAT85,113
J401: XL4016 CC/CV module: IN+ IN- OUT+ OUT-; TerminalBlock_Phoenix_MKDS-1,5-4-5.08_1x04_P5.08mm_Horizont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
J402: XL4016 FB tap (wire to FB pin, GND); JST_XH_B2B-XH-A_1x02_P2.50mm_Vertical
R401: 1.2k; R_1206_3216Metric
R402: 100R; R_1206_3216Metric
U401: MCP4725 module #2 (A0=VCC, 0x61): VCC GND SCL SDA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; PinSocket_1x06_P2.54mm_Vertical

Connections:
+3V3: U401.1, U401.5; also elsewhere on the board
/Charger/CHG_INJ: D401.2 (A), R401.2
/Charger/DAC_C: R402.1, U401.6
/Charger/DAC_CF: C401.1, R401.1, R402.2
/Charger/XL_FB: D401.1 (K), J402.1
CHG_OUT: J401.3; also elsewhere on the board
GND: C401.2, J401.2, J401.4, J402.2, U401.2; also elsewhere on the board
SCL: U401.3; also elsewhere on the board
SDA: U401.4; also elsewhere on the board
VIN: J401.1; also elsewhere on the board

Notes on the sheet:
Set the module CV pot to 4.25 V with no load BEFORE wiring the FB tap. That pot value is the hardware voltage ceiling.
DAC #2 (0x61) injects current into the XL4016 FB pin (1.25 V) through D401 + R401. Injection can only LOWER the output, so DAC = 0 / MCU dead = 4.25 V ceiling, never higher.
With the module bottom FB resistor ~360 Ohm and top ~860 Ohm: DAC 0 V -> 4.25 V, DAC 3.3 V -> ~3.0 V. Measure your module and adjust R401.
The module own CC shunt is bypassed because IN- and OUT- share system GND. Turn its CC pot to max; current is regulated by firmware (ADS1115 + shunt) and limited by the OC comparator.
Firmware CC/CV: lower/raise the DAC until measured current = target, then hold 4.2 V and stop at C/20 by opening K1.
v0.3 REVIEW NOTES - explained in docs/SCHEMATIC_GUIDE.md section 4; checklist with comment columns in docs/SCHEMATIC_REVIEW.md
How it works: XL4016 holds FB = 1.25 V. Current injected into FB (DAC -> R402 -> R401 -> D401) makes the output LOWER. DAC = 0 -> pot setting (4.25 V).
CHECK C-01: NO hardware charge-current limit (module CC bypassed); only the 6.4 A comparator. Firmware must match voltages before closing K1.
CHECK C-02: measure your module FB resistors; the 360 / 860 Ohm values are assumed.
